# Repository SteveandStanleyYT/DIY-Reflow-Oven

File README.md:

# DIY Reflow Oven
## Objective
We are going to be building a lot of SMD PCBs in the future and so we would want to invest in a reflow oven. But the current consumer reflow ovens are very expensive and also require a lot of mods to get them working well. For these reasons, we decided to build our own reflow oven. 

## Requirements
- It should be able to fit a medium-sized board.
- It should look aesthetically pleasing (Wires should not be dangling around.)

## Components
| Component                                 | Link                                                                                                                      | 
|-------------------------------------------|---------------------------------------------------------------------------------------------------------------------------|
| Hamilton Beach toaster oven               | [Link](https://www.amazon.com/gp/product/B08CW95ZFR/ref=ewc_pr_img_1?smid=ATVPDKIKX0DER&psc=1)                            | 
| Panasonic Solid State relay (AQA211VL)    | [AQA211VL](https://www.digikey.com/en/products/detail/panasonic-electric-works/AQA211VL/2364682)                           | 
| RTD PT100 Sensor                          | [Link](https://www.amazon.com/T-PRO-Bonded-PT100-Sensor-3-3Ft/dp/B08LM65RR9/ref=sr_1_1_sspa?dib=eyJ2IjoiMSJ9.ho2rK_0WDDtzblfta3BW38M7qYvQeWUQCptRPbSS0BLeCsDtmtxTRNIGxjzQsyyU5wBJDnWwgiXgdA0Wa3jods1JWFmNPTgaX-OKxc_kS5rdJuIUgGGF4iHpwLhBHd4v9ZD8DF-NOKP-BuiiUtAb_fOJcZcli_CCJBb9d0RBt79JrkZgC5OPRpzAKGa2WIGDiQFRGdwM_pzMzyg8votbx8N-DyOa5gWSov0g3i_Jxe4.gcv0qolQDvdorbPu7aZP2Ob7Y0XtCTAz7jK61YfO9O4&dib_tag=se&keywords=pt100+rtd&qid=1749510461&sr=8-1-spons&sp_csd=d2lkZ2V0TmFtZT1zcF9hdGY&psc=1)                                                                                                                         |  
| MAX31865 RTD Temperature Thermocouple      | [Link](https://www.amazon.com/HiLetgo-MAX31865-Temperature-Thermocouple-Amplifier/dp/B071DVVZHC/ref=pd_bxgy_d_sccl_2/135-4655259-4365117?pd_rd_w=0znua&content-id=amzn1.sym.de9a1315-b9df-4c24-863c-7afcb2e4cc0a&pf_rd_p=de9a1315-b9df-4c24-863c-7afcb2e4cc0a&pf_rd_r=BFC7F3X7E3RN3DVGXN7T&pd_rd_wg=TNM6I&pd_rd_r=45f8c50e-10f0-4ade-a76b-58bd8f712acb&pd_rd_i=B071DVVZHC&psc=1) |
| Ceramic Blanket                           | [Link](https://www.aliexpress.us/item/3256802930270704.html?spm=a2g0o.cart.0.0.20b138da8MZPSK&mp=1&gatewayAdapt=glo2usa)   | 
| Aluminum reflective tape                  | —                                                                                                                         | 
| 240×320 SPI Display                       | —                                                                                                                         | 
| ESP32                                     | —                                                                                                                         | 
| 12V 1A Power Supply                       | [Link](https://www.aliexpress.us/item/3256802541723599.html?spm=a2g0o.cart.0.0.390f38daALcrNV&mp=1&gatewayAdapt=glo2usa)   | 
| Cooling Fan                               | —                                                                                                                         | 
| Green LED                                 | [Link](https://www.digikey.com/en/products/detail/lumex-opto-components-inc/SSI-LXH1090GD/144696)| 
| Red LED                                   | [Link](https://www.digikey.com/en/products/detail/lumex-opto-components-inc/SSI-LXH1090SRD/144702)| 
| Buzzer                                    | —                                                                                                                         |
| Switch                                    | —                                                                                                                         | 
| Relay                                     | —                                                                                                                         |
| Terminal Blocks                           | —                                                                                                                         | 
| USB-C to Micro USB cable                  | -                                                                                                                |

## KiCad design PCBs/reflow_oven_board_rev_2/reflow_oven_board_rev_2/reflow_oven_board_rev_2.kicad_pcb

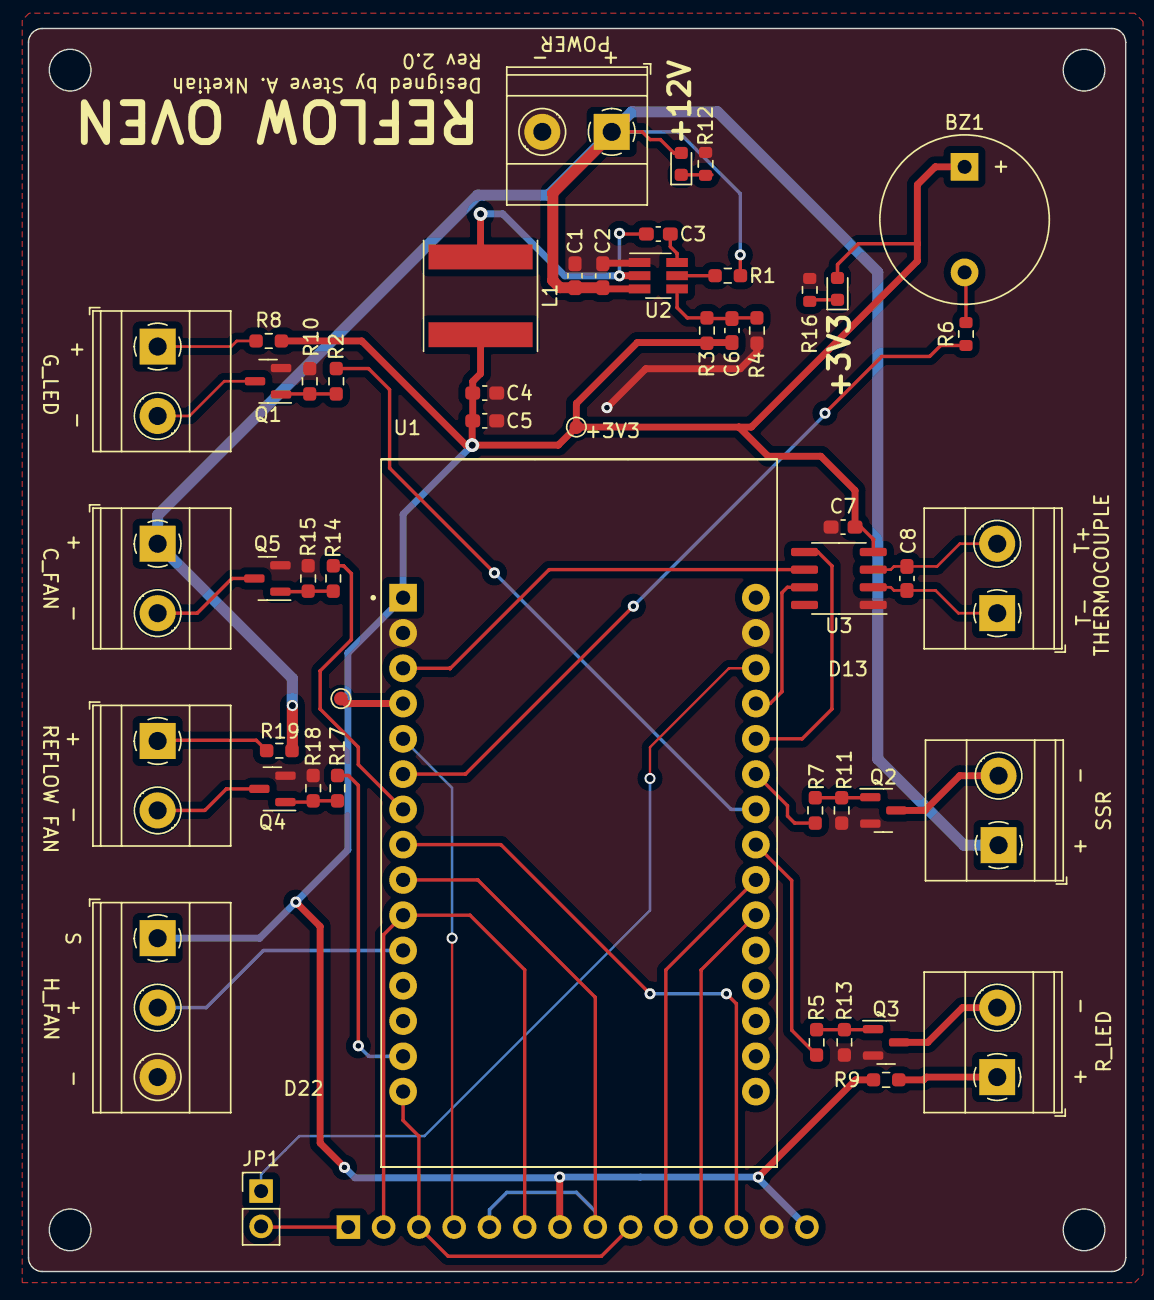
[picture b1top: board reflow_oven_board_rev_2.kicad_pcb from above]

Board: 2 copper layers, 79.0 x 89.5 mm, 51 parts (1 on the bottom side), 45 nets.

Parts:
BZ1: Buzzer; Buzzer_12x9.5RM7.6
C1: 10u; C_0603_1608Metric_Pad1.08x0.95mm_HandSolder
C2, C3, C7: 0.1u; C_0603_1608Metric_Pad1.08x0.95mm_HandSolder
C4, C5: 22u; C_0603_1608Metric_Pad1.08x0.95mm_HandSolder
C6: 56p; C_0603_1608Metric_Pad1.08x0.95mm_HandSolder
C8: 10nF; C_0603_1608Metric_Pad1.08x0.95mm_HandSolder
D1, D2: LED; LED_0603_1608Metric
J1: PinSocket_1x14_P2.54mm_Vertical
J2, J3, J4, J5, J6, J7, J9: TerminalBlock_Phoenix_MKDS-1,5-2_1x02_P5.00mm_Horizontal
J8: Screw_Terminal_01x03; TerminalBlock_Phoenix_MKDS-1,5-3_1x03_P5.00mm_Horizontal
JP1: SolderJumper_2_Open; PinHeader_1x02_P2.54mm_Vertical
L1: 15u; L_Taiyo-Yuden_NR-80xx
Q1, Q2, Q3, Q4, Q5: DMG3402L; SOT-23
R1: 510k; R_0603_1608Metric_Pad0.98x0.95mm_HandSolder
R2, R5, R7, R14, R17: 150; R_0603_1608Metric_Pad0.98x0.95mm_HandSolder
R3: 100k; R_0603_1608Metric_Pad0.98x0.95mm_HandSolder
R4: 22.1k; R_0603_1608Metric_Pad0.98x0.95mm_HandSolder
R6: 0; R_0603_1608Metric
R8, R9: 60.4; R_0603_1608Metric_Pad0.98x0.95mm_HandSolder
R10, R11, R13, R15, R18: 10k; R_0603_1608Metric_Pad0.98x0.95mm_HandSolder
R12: 1k; R_0603_1608Metric
R16: 150; R_0603_1608Metric
R19: 0; R_0603_1608Metric_Pad0.98x0.95mm_HandSolder
TP3, TP4: TestPoint_Alt; TestPoint_Pad_D1.0mm
U1: ESP32-DEVKIT-V1; MODULE_ESP32_DEVKIT_V1
U2: TPS54202HDDCR; SOT-23-6_Handsoldering
U3: MAX31855KASA; SOIC-8_3.9x4.9mm_P1.27mm

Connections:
+3V3: BZ1.1 (+), C4.1, C5.1, C6.1, C7.1, D2.2 (A), J1.7, J1.14, J8.1, L1.2, R3.1, R8.1, R9.1, TP4.1, U1.1 (3V3), U3.4 (V_CC)
+12V: C1.1, C2.1, D1.2 (A), J5.1, J6.1, J9.1, R1.1, R19.1, U2.3 (VIN)
/BOOT: C3.1, U2.6 (BOOT)
/BUZZ_D: BZ1.2 (-), R6.2
/CF_D: J9.2, Q5.3 (D)
/CF_G: Q5.1 (G), R14.2, R15.1
/EN: R1.2, U2.5 (EN)
/FB: C6.2, R3.2, R4.1, U2.4 (FB)
/GLED+: J3.1, R8.2
/GLED-: J3.2, Q1.3 (D)
/GLED_G: Q1.1 (G), R2.2, R10.1
/RLED+: J4.1, R9.2
/RLED-: J4.2, Q3.3 (D)
/RLED_G: Q3.1 (G), R5.2, R13.1
/R_C+: J7.1, R19.2
/R_C-: J7.2, Q4.3 (D)
/R_C_G: Q4.1 (G), R17.2, R18.1
/SSR_D: J5.2, Q2.3 (D)
/SSR_G: Q2.1 (G), R7.2, R11.1
/SW: C3.2, L1.1, U2.2 (SW)
/T+: C8.1, J2.2, U3.3 (T+)
/T-: C8.2, J2.1, U3.2 (T-)
BUZZER: R6.1, U1.6 (RX2)
CS: J1.12, U1.8 (D5)
C_FAN: R14.1, U1.7 (TX2)
D/C: J1.10, U1.22 (D33)
GND: C1.2, C2.2, C4.2, C5.2, C7.2, J1.13, J6.2, J8.3, Q1.2 (S), Q2.2 (S), Q3.2 (S), Q4.2 (S), Q5.2 (S), R4.2, R10.2, R11.2, R12.2, R13.2, R15.2, R16.2, R18.2, U1.2 (GND), U1.29 (GND), U2.1 (GND), U3.1 (GND)
G_LED: R2.1, U1.24 (D26)
H_FAN: J8.2, U1.11 (D21)
M_CS: U1.3 (D15), U3.6 (~CS)
M_MISO: U1.27 (D12), U3.7 (SO)
M_SCK: U1.26 (D14), U3.5 (SCK)
unnamed: D1.1 (K), R12.1
unnamed: D2.1 (K), R16.1
unnamed: JP1.1 (A), U1.28 (D13)
unnamed: TP3.1, U1.4 (D2)
REFLOW_C_FAN: R17.1, U1.14 (D22)
RESET: J1.11, U1.21 (D32)
R_LED: R5.1, U1.23 (D25)
SCK: J1.5, J1.8, U1.9 (D18)
SDI: J1.3, J1.9, U1.15 (D23)
SDO: J1.2, J1.6, U1.10 (D19)
SSR: R7.1, U1.25 (D27)
T_CS: J1.4, U1.5 (D4)
T_IRQ: J1.1, JP1.2 (B)

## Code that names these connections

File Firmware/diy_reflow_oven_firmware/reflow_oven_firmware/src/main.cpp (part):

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
Adafruit_MAX31865 thermo = Adafruit_MAX31865(15, 13, 12, 14);

const int red_led = 25, green_led = 26, ssr = 27, buzzer = 16, cooling_fan = 27, h_fan = 21;

const int SSR_FREQ = 10, ssr_channel = 0, resolution = 8;

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  // put your setup code here, to run once:
  pinMode(red_led, OUTPUT);
  pinMode(green_led, OUTPUT);
  pinMode(ssr, OUTPUT);
  pinMode(buzzer, OUTPUT);
  pinMode(cooling_fan, OUTPUT);
  pinMode(h_fan, OUTPUT);
  ledcSetup(ssr_channel, SSR_FREQ, resolution);
  ledcAttachPin(ssr, ssr_channel);
  Serial.begin(115200);
  tft.init();
  tft.setRotation(0);
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
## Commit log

2025-06-09 Initial Commit.
2025-06-09 Remove ZIP backups and ignore them
2025-06-09 readme edits
